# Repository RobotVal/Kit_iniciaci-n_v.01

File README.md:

# Kit_iniciaci-n_v.01
kit iniciación

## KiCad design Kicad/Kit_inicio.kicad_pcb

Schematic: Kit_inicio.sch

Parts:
BZ1: Buzzer; Buzzer_12x9.5RM7.6
C1: 470uF; C_0805
C2: 1 uF; C_0805
C3: 0.1uF; C_0805
J1: BT; Pin_Header_Straight_1x04_Pitch2.54mm
J2: Temp; Pin_Header_Straight_1x03_Pitch2.54mm
J3: Gp2y0; Pin_Header_Straight_1x03_Pitch2.54mm
J4: CNY_Flex; TE_84952-8_1x08_P1.0mm_Horizontal
J5: Front_flex; TE_84952-8_1x08_P1.0mm_Horizontal
J6: Conn_Mot1; Pin_Header_Straight_1x02_Pitch2.54mm
J7: Conn_Mot2; Pin_Header_Straight_1x02_Pitch2.54mm
J8, J9, J10, J15: Conn_01x03; Pin_Header_Straight_1x03_Pitch2.54mm
J11: Jumper; Pin_Header_Straight_1x02_Pitch2.54mm
J12: Ultrasonidos; Pin_Header_Straight_1x04_Pitch2.54mm
J13, J14: Conn_01x15; Pin_Header_Straight_1x15_Pitch2.54mm
J16: Conn_Bat; Pin_Header_Straight_1x02_Pitch2.54mm
JP1: Jumper; Pin_Header_Straight_1x02_Pitch2.54mm
Q1: IRF5305; TO-220-3_Vertical
R1, R2, R3, R7, R8, R9, R14, R17, R19, R21: 220; R_0805
R4, R5, R6, R10, R11, R12, R13, R15, R18, R20, R22: 10K; R_0805
SW1: SW_Push; PCB_PUSH
U1, U2, U3, U4, U5, U6, U11, U12, U13, U14: CNY70; QRE1113GRCT-ND
U7: Arduino_Nano_R3; Arduino_nano
U8: TB6612FNG; SSOP-24_5.3x8.2mm_Pitch0.65mm
U9: Booster12V; Driver_XL6000w
U10: L7805; TO-126_Vertical

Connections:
+5V: C3.1, J1.4, J2.1, J3.1, J4.1, J5.1, J12.1, J13.4, SW1.1, U1.1, U1.3, U2.1, U2.3, U3.1, U3.3, U4.1, U4.3, U5.1, U5.3, U6.1, U6.3, U7.12 (5V), U8.20 (VCC), U10.3
/3V3: J13.14, U7.2 (3V3)
/A0: J5.2, J13.12, U7.4 (A0)
/A1: J5.3, J13.11, U7.5 (A1)
/A2: J5.4, J13.10, U7.6 (A2)
/A3: J5.5, J13.9, U7.7 (A3)
/A4: J5.6, J13.8, U7.8 (A4)
/A5: J5.7, J13.7, U7.9 (A5)
/A6: J2.2, J13.6, JP1.1, U7.10 (A6)
/A7: J13.5, U7.11 (A7)
/AREF: J13.13, U7.3 (AREF)
/Bat+: J16.2, Q1.2 (D)
/D0: J1.2, J14.14, U7.17 (D0/RX)
/D1: J1.1, J14.15, U7.16 (D1/TX)
/D2: J11.1, J14.11, U7.20 (D2)
/D3: J14.10, R13.2, SW1.2, U7.21 (D3)
/D4: J14.9, U7.22 (D4)
/D5: J12.2, J14.8, U7.23 (D5)
/D6: J12.3, J14.7, U7.24 (D6), U8.23 (PWMA)
/D7: J14.6, U7.25 (D7), U8.21 (AIN1)
/D8: J14.5, U7.26 (D8), U8.22 (AIN2)
/D9: J14.4, U7.27 (D9), U8.17 (BIN1)
/D10: J14.3, U7.28 (D10), U8.16 (BIN2)
/D11: J14.2, U7.29 (D11/MOSI), U8.15 (PWMB)
/D12: J14.1, U7.30 (D12/MISO)
/D13: J13.15, U7.1 (D13/SCK)
/Mot_A1: J6.1, U8.1 (AO1), U8.2 (AO1)
/Mot_A2: J6.2, U8.5 (AO2), U8.6 (AO2)
/Mot_B1: J7.1, U8.11 (BO1), U8.12 (BO1)
/Mot_B2: J7.2, U8.7 (BO2), U8.8 (BO2)
/RST: J13.3, J14.13, U7.13 (RESET), U7.18 (RESET)
/S0: J4.2, R6.2, U3.4
/S1: J4.3, R12.2, U6.4
/S2: J4.4, R5.2, U2.4
/S3: J4.5, R11.2, U5.4
/S4: J4.6, R4.2, U1.4
/S5: J4.7, R10.2, U4.4
/V_mot: U8.13 (VM2), U8.14 (VM3), U8.24 (VM1), U9.3 (Vout)
/Vin: J13.1, U7.15 (VIN), U9.1 (Vin)
unnamed: BZ1.1, J11.2
unnamed: C1.1, C2.1, Q1.3 (S), U10.1
unnamed: J3.2, JP1.2
unnamed: J8.1, R17.2, R18.1
unnamed: J8.2, R18.2, U11.4
unnamed: J8.3, U11.1, U11.3
unnamed: J9.1, R19.2, R20.1
unnamed: J9.2, R20.2, U12.4
unnamed: J9.3, U12.1, U12.3
unnamed: J10.1, R21.2, R22.1
unnamed: J10.2, R22.2, U13.4
unnamed: J10.3, U13.1, U13.3
unnamed: J15.1, R14.2, R15.1
unnamed: J15.2, R15.2, U14.4
unnamed: J15.3, U14.1, U14.3
unnamed: R1.1, U1.2
unnamed: R2.1, U2.2
unnamed: R3.1, U3.2
unnamed: R7.1, U4.2
unnamed: R8.1, U5.2
unnamed: R9.1, U6.2
unnamed: R14.1, U14.2
unnamed: R17.1, U11.2
unnamed: R19.1, U12.2
unnamed: R21.1, U13.2

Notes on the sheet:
Calcular las intensidades para ver si podemos utilizar 7805 SMD
- pin +

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
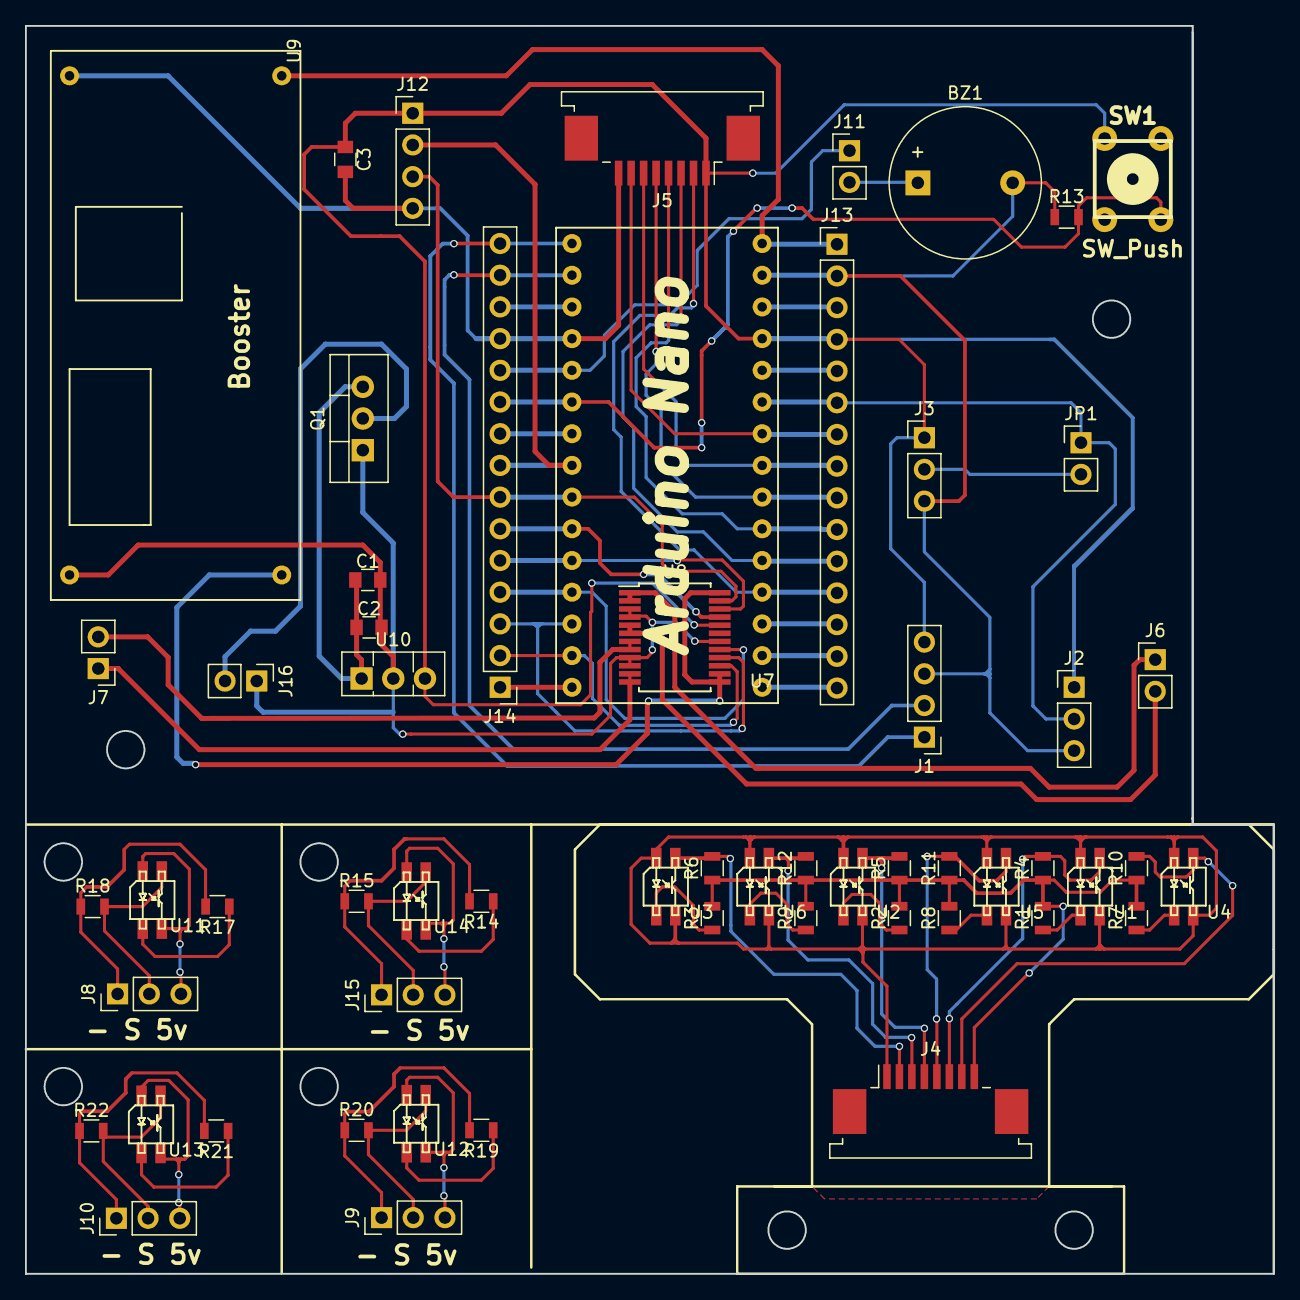
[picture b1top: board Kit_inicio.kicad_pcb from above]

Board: 2 copper layers, 100.0 x 100.0 mm, 58 parts (0 on the bottom side), 65 nets.

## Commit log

2018-10-15 R
    R
2018-10-15 Kicad_15_10_1230
2018-10-15 15_10_12_20
    Kicad terminado por revisar conectores y baterias
2018-10-16 Kicad Kit Inicio
